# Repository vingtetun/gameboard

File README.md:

# GameBoard
## GamePlay Instructions
* Download Repo. You can click the 'Download Zip' button on the right.
* Install dependencies with `npm install`.
* Run the server with: `npm start`
* Navigate to: http://localhost:8001
* Select to play either the automated demo or a real, turn-based game.

Or play me live using Firefox at https://kglazko.github.io/gameboard/

## Using the spinner

Ensure the spinner is plugged in via USB and instead start the server with:
* `USE_SPINNER=1 npm start`
* Spinning the spinner will automatically trigger a turn for the active player.

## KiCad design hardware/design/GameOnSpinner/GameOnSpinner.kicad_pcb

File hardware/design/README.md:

Hardware design files for GameON.

All files are currently designed in KiCad (http://kicad-pcb.org/).

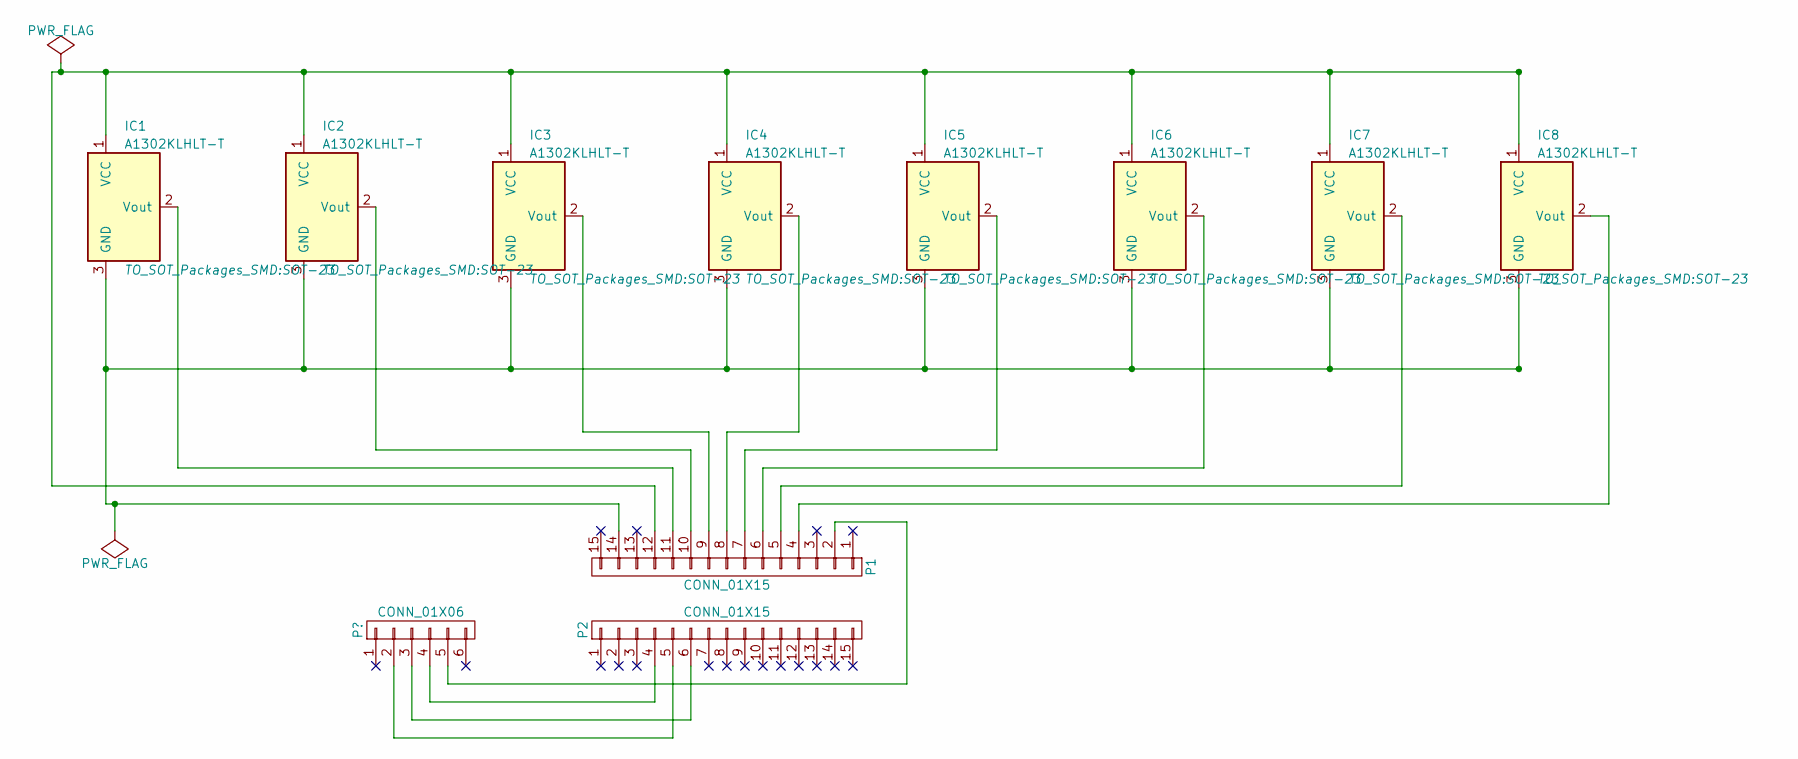
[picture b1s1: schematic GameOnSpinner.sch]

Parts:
IC1, IC2, IC3, IC4, IC5, IC6, IC7, IC8: A1302KLHLT-T; SOT-23
P1, P2: CONN_01X15; Socket_Strip_Straight_1x15

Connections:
unnamed: IC1.1 (VCC), IC2.1 (VCC), IC3.1 (VCC), IC4.1 (VCC), IC5.1 (VCC), IC6.1 (VCC), IC7.1 (VCC), IC8.1 (VCC), P1.12
unnamed: IC1.2 (Vout), P1.11
unnamed: IC1.3 (GND), IC2.3 (GND), IC3.3 (GND), IC4.3 (GND), IC5.3 (GND), IC6.3 (GND), IC7.3 (GND), IC8.3 (GND), P1.14
unnamed: IC2.2 (Vout), P1.10
unnamed: IC3.2 (Vout), P1.9
unnamed: IC4.2 (Vout), P1.8
unnamed: IC5.2 (Vout), P1.7
unnamed: IC6.2 (Vout), P1.6
unnamed: IC7.2 (Vout), P1.5
unnamed: IC8.2 (Vout), P1.4
unnamed 11: P1.2; also elsewhere on the board
unnamed 18: P2.4; also elsewhere on the board
unnamed 19: P2.5; also elsewhere on the board
unnamed 20: P2.6; also elsewhere on the board

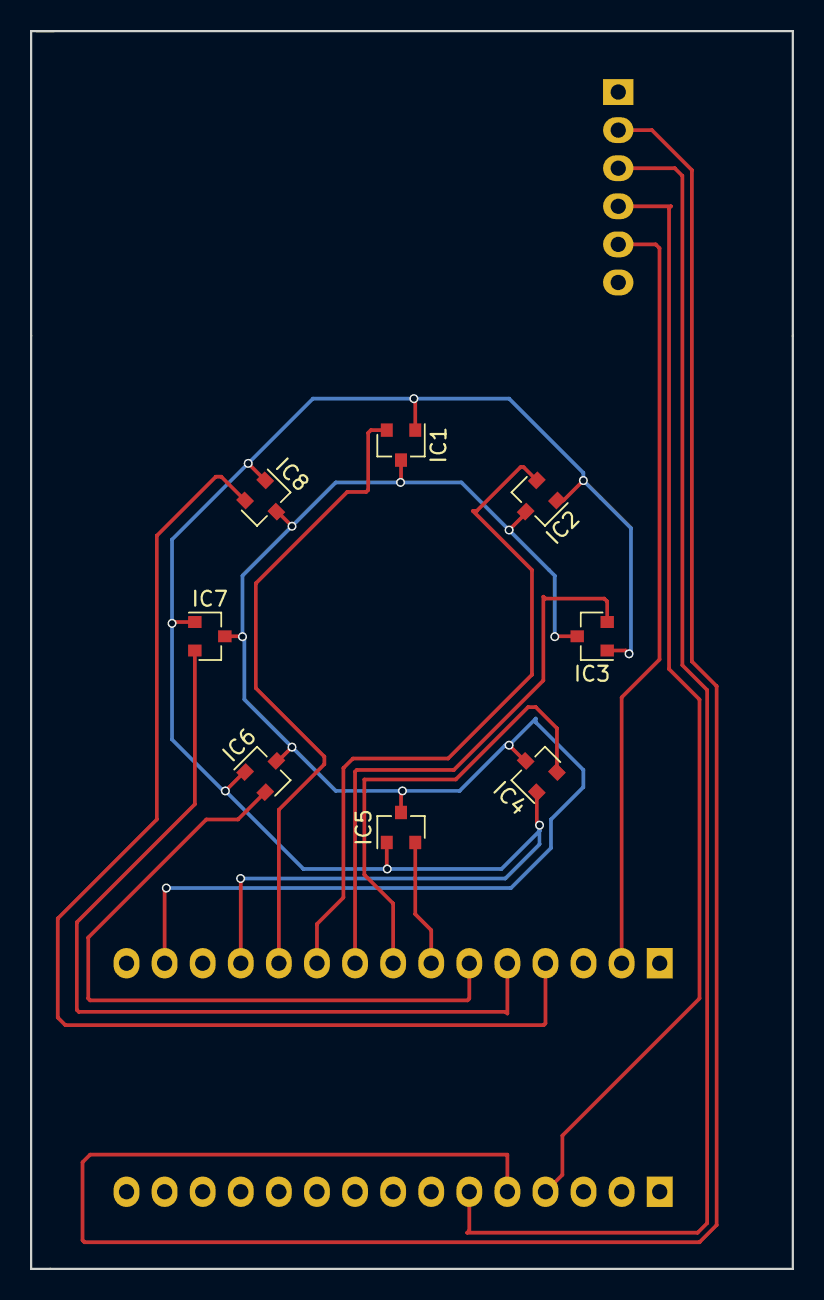
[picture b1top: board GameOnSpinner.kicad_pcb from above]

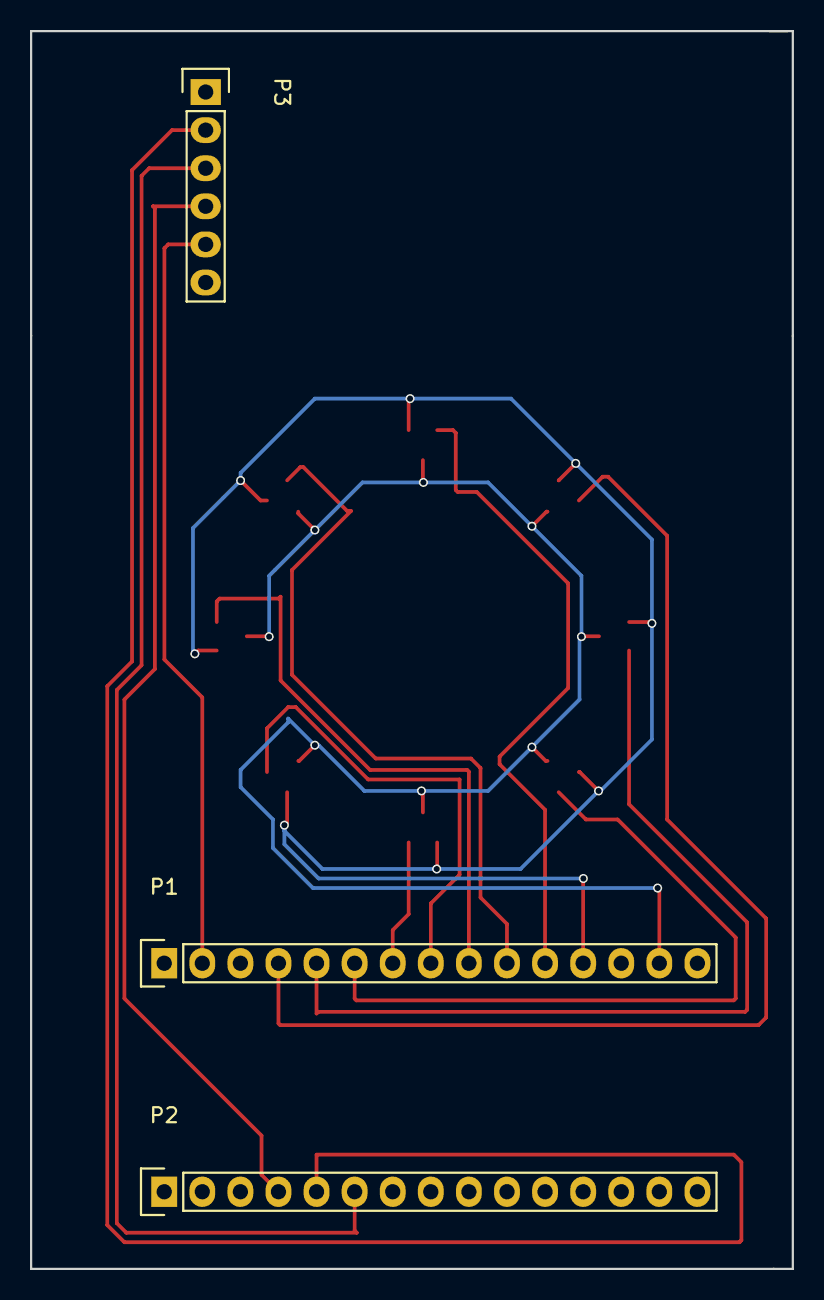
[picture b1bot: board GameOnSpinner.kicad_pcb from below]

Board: 2 copper layers, 50.8 x 82.5 mm, 11 parts (3 on the bottom side), 14 nets.

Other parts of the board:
P3: CONN_01X06; Socket_Strip_Straight_1x06

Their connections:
unnamed 11: P3.5; also elsewhere on the board
unnamed 18: P3.4; also elsewhere on the board
unnamed 19: P3.2; also elsewhere on the board
unnamed 20: P3.3; also elsewhere on the board

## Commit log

2016-10-10 Initial commit of a gameboard simulator
2016-10-11 Added switch logic
2016-10-11 Added squares and LEDS
2016-10-11 Committing attempt at lighting up 1 square
2016-10-11 Added a fix but still weird
2016-10-11 Change that made a fix
2016-10-12 Add some examples to update individual case and/or range of cases
2016-10-12 Added rng and initial LED turn logic
2016-10-12 Added timer and game state logic
2016-10-12 Initial automated gameplay work completed.
2016-10-12 Fixed bug
2016-10-12 2 Player automated gameplay
2016-10-12 Added 3rd player support.
2016-10-12 Pushing new branch
2016-10-12 Added endstate code
2016-10-12 New branch
2016-10-12 Added snakes and ladders functionality
2016-10-13 added buttons yeah
2016-10-13 Refact0red
2016-10-13 Changed read
2016-10-13 Changed Chutes and ladders behavior
2016-10-13 POLISHING WORKS
2016-10-13 Fixed the special case logic
2016-10-13 Added marker parts
2016-10-14 Integrate the demo branch. Added the composition.js file to make clearer the difference between update/paint.
2016-10-14 Add scripts/key_shortcuts.js to keep index.js in sync with the node version
2016-10-14 Added turn and automation buttons and start over button
2016-10-14 Add sound to master
2016-10-14 Finalized sounds
2016-10-14 Need to add the readme though
2016-10-14 Added choose a player
2016-10-14 Color swap
2016-10-14 Small fix for buttons
2016-10-17 Get it working on node again. Add game-server/ folder to run a local websocket server and change the game to use that as the source of trust for connected players.
2016-10-17 Fix key_shortcuts.js to not send a move command on Ctrl+Shift+R
2016-10-17 Keep local play working if the game can not connect to a remote endpoint
2016-10-24 Setup game server and make web sockets compatible with express.
2016-10-26 Added the illustrations
2016-10-26 Changed player position
2016-10-26 Fixed
2016-10-26 Hook up spinner and broadcast moves.
2016-10-26 Update readme for spinner.
2016-10-26 Add example hall sensor test.
2016-10-26 Remove comment.
2016-11-04 Checkers starter code not working still fixing
2016-11-07 Got checkers to render
2016-11-14 Checker class up and rendering
2016-11-16 Added gameplay code
2016-11-16 Wrong case ID being returned on click
2016-11-17 Very close now
2016-11-17 Preliminary click to move
2016-11-17 Still fixing
2016-11-21 Moving math fixed
2016-11-21 Checkers rules start
2016-11-22 Jumping works for red side checkers
2016-12-08 Add game on spinner schematic and pcb files.
2016-12-08 Proper spacing for hall sensors.
2016-12-08 Position header strips for nano.
2016-12-08 Add outline.
2016-12-08 Routing.
2016-12-08 Not working yet
2016-12-08 Add bluetooth board.
2016-12-08 Add gerber files.
2016-12-09 Initial board /w LCD screen header.
